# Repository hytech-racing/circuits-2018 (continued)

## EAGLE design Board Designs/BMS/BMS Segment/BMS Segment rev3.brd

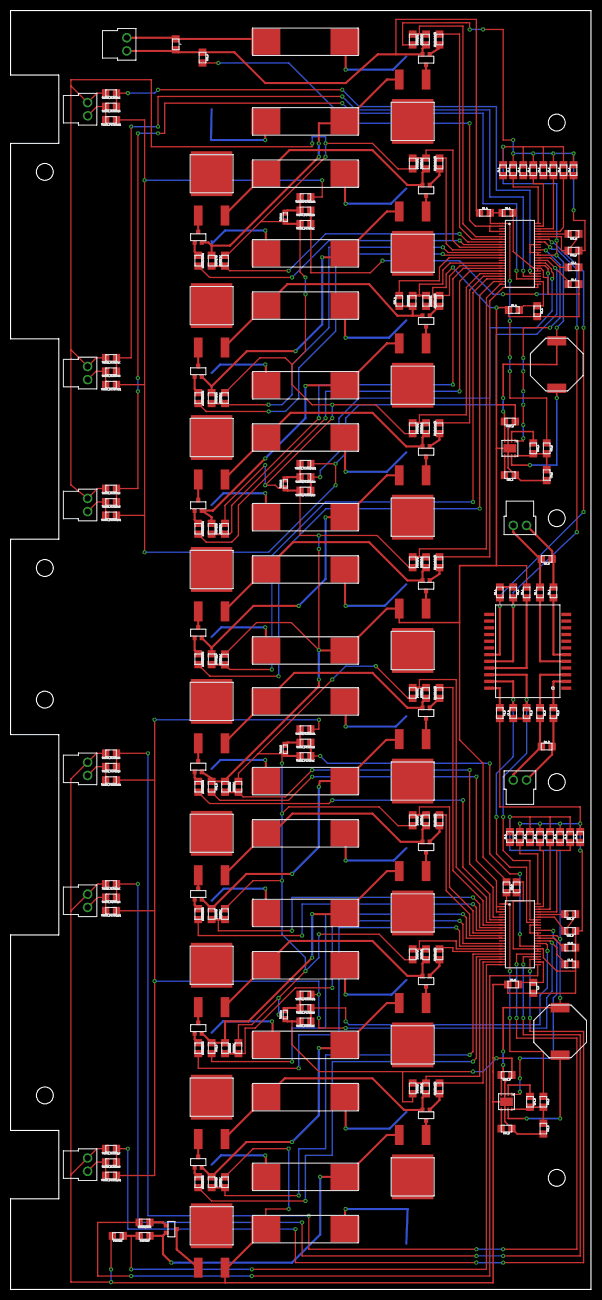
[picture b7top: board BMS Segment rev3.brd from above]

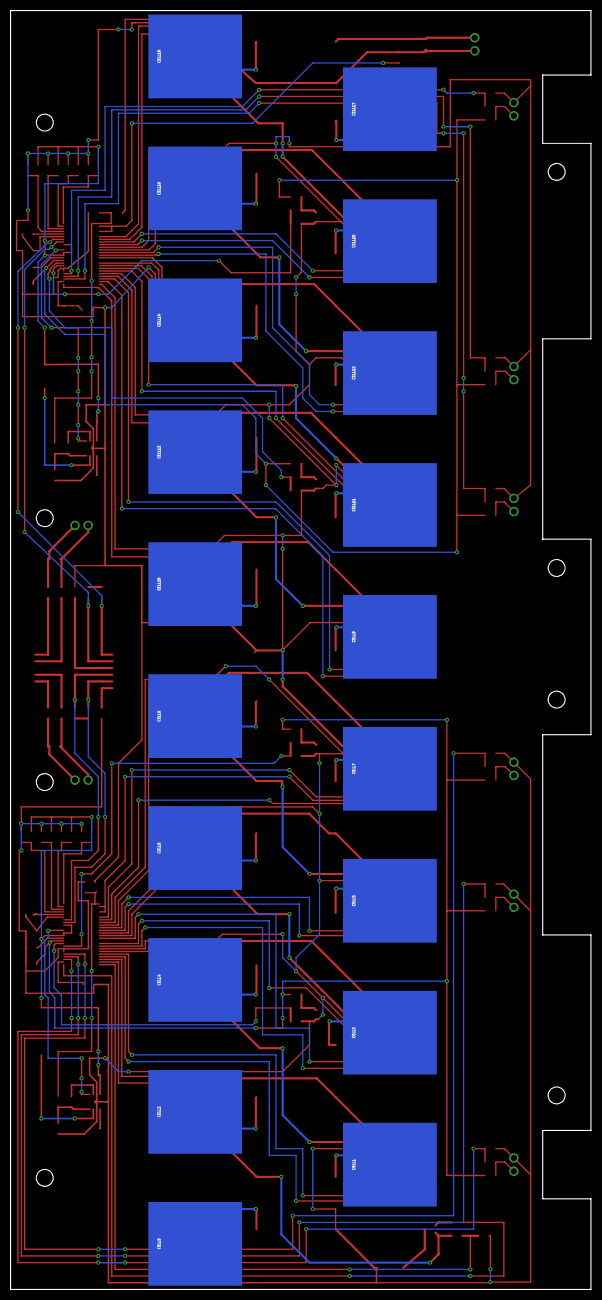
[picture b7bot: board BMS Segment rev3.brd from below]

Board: 2 copper layers, 110.0 x 242.3 mm, 237 parts (19 on the bottom side), 183 nets.

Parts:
AMS_TEST_PORT1: CONNECTOR-2NANO-FIT_VERTICAL-2; NANO-FIT_VERTICAL-2
BUCK_CONV_A: ADP2360; LFCSP-8
BUCK_CONV_B: ADP2360; LFCSP-8
C1_A, C1_B, C2_A, C2_B: 1uF; 0805
C3_A, C3_B: 15pF; 0805
C4_A, C4_B, C5_A: 10nF; 0805
C6_A, C6_B: 0.1uF; 0805
CELL0, CELL1, CELL2, CELL3, CELL4, CELL5, CELL6, CELL7, CELL8, CELL9, CELL10, CELL11, CELL12, CELL13, CELL14, CELL15, CELL16, CELL17, CELL18: BATTERY_SPRING_KEYSTONE5222; KEYSTONE5222
CIN_A: 4.7uF; 0805
CIN_B: 4.7uF; 0805
COUT_A: 22uF; 0805
COUT_B: 22uF; 0805
CSS_A: 2.2nF; 0805
CSS_B: 2.2nF; 0805
C_5: 10nF; 0805
DRAIN1:C, DRAIN2:C, DRAIN3:C, DRAIN4:C, DRAIN5:C, DRAIN6:C, DRAIN7:C, DRAIN8:C, DRAIN9:C, DRAIN10:C, DRAIN11:C, DRAIN12:C, DRAIN13:C, DRAIN14:C, DRAIN15:C, DRAIN16:C, DRAIN17:C, DRAIN18:C: 10nF; 0805
DRAIN1:DISCHARGE, DRAIN2:DISCHARGE, DRAIN3:DISCHARGE, DRAIN4:DISCHARGE, DRAIN5:DISCHARGE, DRAIN6:DISCHARGE, DRAIN7:DISCHARGE, DRAIN8:DISCHARGE, DRAIN9:DISCHARGE, DRAIN10:DISCHARGE, DRAIN11:DISCHARGE, DRAIN12:DISCHARGE, DRAIN13:DISCHARGE, DRAIN14:DISCHARGE, DRAIN15:DISCHARGE, DRAIN16:DISCHARGE, DRAIN17:DISCHARGE, DRAIN18:DISCHARGE: 5Ω; PWR163
DRAIN1:GATE, DRAIN2:GATE, DRAIN3:GATE, DRAIN4:GATE, DRAIN5:GATE, DRAIN6:GATE, DRAIN7:GATE, DRAIN8:GATE, DRAIN9:GATE, DRAIN10:GATE, DRAIN11:GATE, DRAIN12:GATE, DRAIN13:GATE, DRAIN14:GATE, DRAIN15:GATE, DRAIN16:GATE, DRAIN17:GATE, DRAIN18:GATE: 3.3kΩ; 0805
DRAIN1:PFET, DRAIN2:PFET, DRAIN3:PFET, DRAIN4:PFET, DRAIN5:PFET, DRAIN6:PFET, DRAIN7:PFET, DRAIN8:PFET, DRAIN9:PFET, DRAIN10:PFET, DRAIN11:PFET, DRAIN12:PFET, DRAIN13:PFET, DRAIN14:PFET, DRAIN15:PFET, DRAIN16:PFET, DRAIN17:PFET, DRAIN18:PFET: P-CHANNEL_MOSFET_DMP3099L-7; SOT23
DRAIN1:R, DRAIN2:R, DRAIN3:R, DRAIN4:R, DRAIN5:R, DRAIN6:R, DRAIN7:R, DRAIN8:R, DRAIN9:R, DRAIN10:R, DRAIN11:R, DRAIN12:R, DRAIN13:R, DRAIN14:R, DRAIN15:R, DRAIN16:R, DRAIN17:R, DRAIN18:R: 100Ω; 0805
F0, F1, F2, F3, F4, F5, F6, F7, F8, F9, F10, F11, F12, F13, F14, F15, F16, F17, F18: 0001.2704.11; 5X20MM_FUSE
ISOSPI_A: CONNECTOR-2NANO-FIT_VERTICAL-2; NANO-FIT_VERTICAL-2
ISOSPI_B: CONNECTOR-2NANO-FIT_VERTICAL-2; NANO-FIT_VERTICAL-2
J, J1_A, J1_B, J2_A, J2_B, J3_A, J3_B, J4_A, J4_B, J5_A, J5_B, J6_A, J6_B, J7_A, J7_B, J8_A, J8_B: 0805
L1_A, L1_B: 330uH; SRU1048
R1_A, R1_B, R2_A, R2_B: 100Ω; 0805
R3_A, R3_B: 402Ω; 0805
R4_A, R4_B, R5_A, R5_B: 22Ω; 0805
RB1_A, RB1_B: 1.2kΩ; 0805
RB2_A, RB2_B: 800Ω; 0805
RIN_A: 1kΩ; 0805
RIN_B: 1kΩ; 0805
RM_A: 100Ω; 0805
RM_B: 100Ω; 0805
RPG_A: 10MΩ; 0805
RPG_B: 10MΩ; 0805
RU1_A, RU1_B, RU2_A, RU2_B: 100Ω; 0805
THERM1, THERM2, THERM3, THERM4: 10kΩ; 0603
THERM1A, THERM1_B: Th1; NANO-FIT_VERTICAL-2
THERM2A, THERM2_B: Th2; NANO-FIT_VERTICAL-2
THERM3A, THERM3_B: Th3; NANO-FIT_VERTICAL-2
THERM_FILTER1:C, THERM_FILTER2:C, THERM_FILTER3:C, THERM_FILTER4:C, THERM_FILTER5:C, THERM_FILTER6:C, THERM_FILTER7:C, THERM_FILTER8:C, THERM_FILTER9:C, THERM_FILTER10:C: 10nF; 0805
THERM_FILTER1:R, THERM_FILTER2:R, THERM_FILTER3:R, THERM_FILTER4:R, THERM_FILTER5:R, THERM_FILTER6:R, THERM_FILTER7:R, THERM_FILTER8:R, THERM_FILTER9:R, THERM_FILTER10:R: 100Ω; 0805
THERM_FILTER1:R1, THERM_FILTER2:R1, THERM_FILTER3:R1, THERM_FILTER4:R1, THERM_FILTER5:R1, THERM_FILTER6:R1, THERM_FILTER7:R1, THERM_FILTER8:R1, THERM_FILTER9:R1, THERM_FILTER10:R1: 10kΩ; 0805
TRANSFORMER: SM51589PEL
U$1, U$2: LTC6804-2; LTC6804

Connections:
C0_A: C5_A.1, R2_A.2, U$1.26
C0_B: C_5.1, R2_B.2, U$2.26
C1_A: DRAIN10:C.1, DRAIN10:R.2, U$1.24
C1_B: DRAIN1:C.1, DRAIN1:R.2, U$2.24
C2_A: DRAIN11:C.1, DRAIN11:R.2, U$1.22
C2_B: DRAIN2:C.1, DRAIN2:R.2, U$2.22
C3_A: DRAIN12:C.1, DRAIN12:R.2, U$1.20
C3_B: DRAIN3:C.1, DRAIN3:R.2, U$2.20
C4_A: DRAIN13:C.1, DRAIN13:R.2, U$1.18
C4_B: DRAIN4:C.1, DRAIN4:R.2, U$2.18
C5_A: DRAIN14:C.1, DRAIN14:R.2, U$1.16
C5_B: DRAIN5:C.1, DRAIN5:R.2, U$2.16
C7_A: DRAIN15:C.1, DRAIN15:R.2, U$1.12
C7_B: DRAIN6:C.1, DRAIN6:R.2, U$2.12
C8_A: DRAIN16:C.1, DRAIN16:R.2, U$1.10
C8_B: DRAIN7:C.1, DRAIN7:R.2, U$2.10
C9_A: DRAIN17:C.1, DRAIN17:R.2, U$1.8
C9_B: DRAIN8:C.1, DRAIN8:R.2, U$2.8
C10_A: DRAIN18:C.1, DRAIN18:R.2, U$1.6
C10_B: DRAIN9:C.1, DRAIN9:R.2, U$2.6
CC0: CELL0.P$1, F0.P$1
CC1: CELL1.P$1, F1.P$1
CC2: CELL2.P$1, F2.P$1
CC3: CELL3.P$1, F3.P$1
CC4: CELL4.P$1, F4.P$1
CC5: CELL5.P$1, F5.P$1
CC6: CELL6.P$1, F6.P$1
CC7: CELL7.P$1, F7.P$1
CC8: CELL8.P$1, F8.P$1
CC9: CELL9.P$1, F9.P$1
CC10: CELL10.P$1, F10.P$1
CC11: CELL11.P$1, F11.P$1
CC12: CELL12.P$1, F12.P$1
CC13: CELL13.P$1, F13.P$1
CC14: CELL14.P$1, F14.P$1
CC15: CELL15.P$1, F15.P$1
CC16: CELL16.P$1, F16.P$1
CC17: CELL17.P$1, F17.P$1
CC18: CELL18.P$1, F18.P$1
DRAIN1:GATE: DRAIN1:GATE.1, DRAIN1:PFET.1
DRAIN1:N$1: DRAIN1:DISCHARGE.1, DRAIN1:PFET.3
DRAIN2:GATE: DRAIN2:GATE.1, DRAIN2:PFET.1
DRAIN2:N$1: DRAIN2:DISCHARGE.1, DRAIN2:PFET.3
DRAIN3:GATE: DRAIN3:GATE.1, DRAIN3:PFET.1
DRAIN3:N$1: DRAIN3:DISCHARGE.1, DRAIN3:PFET.3
DRAIN4:GATE: DRAIN4:GATE.1, DRAIN4:PFET.1
DRAIN4:N$1: DRAIN4:DISCHARGE.1, DRAIN4:PFET.3
DRAIN5:GATE: DRAIN5:GATE.1, DRAIN5:PFET.1
DRAIN5:N$1: DRAIN5:DISCHARGE.1, DRAIN5:PFET.3
DRAIN6:GATE: DRAIN6:GATE.1, DRAIN6:PFET.1
DRAIN6:N$1: DRAIN6:DISCHARGE.1, DRAIN6:PFET.3
DRAIN7:GATE: DRAIN7:GATE.1, DRAIN7:PFET.1
DRAIN7:N$1: DRAIN7:DISCHARGE.1, DRAIN7:PFET.3
DRAIN8:GATE: DRAIN8:GATE.1, DRAIN8:PFET.1
DRAIN8:N$1: DRAIN8:DISCHARGE.1, DRAIN8:PFET.3
DRAIN9:GATE: DRAIN9:GATE.1, DRAIN9:PFET.1
DRAIN9:N$1: DRAIN9:DISCHARGE.1, DRAIN9:PFET.3
DRAIN10:GATE: DRAIN10:GATE.1, DRAIN10:PFET.1
DRAIN10:N$1: DRAIN10:DISCHARGE.1, DRAIN10:PFET.3
DRAIN11:GATE: DRAIN11:GATE.1, DRAIN11:PFET.1
DRAIN11:N$1: DRAIN11:DISCHARGE.1, DRAIN11:PFET.3
DRAIN12:GATE: DRAIN12:GATE.1, DRAIN12:PFET.1
DRAIN12:N$1: DRAIN12:DISCHARGE.1, DRAIN12:PFET.3
DRAIN13:GATE: DRAIN13:GATE.1, DRAIN13:PFET.1
DRAIN13:N$1: DRAIN13:DISCHARGE.1, DRAIN13:PFET.3
DRAIN14:GATE: DRAIN14:GATE.1, DRAIN14:PFET.1
DRAIN14:N$1: DRAIN14:DISCHARGE.1, DRAIN14:PFET.3
DRAIN15:GATE: DRAIN15:GATE.1, DRAIN15:PFET.1
DRAIN15:N$1: DRAIN15:DISCHARGE.1, DRAIN15:PFET.3
DRAIN16:GATE: DRAIN16:GATE.1, DRAIN16:PFET.1
DRAIN16:N$1: DRAIN16:DISCHARGE.1, DRAIN16:PFET.3
DRAIN17:GATE: DRAIN17:GATE.1, DRAIN17:PFET.1
DRAIN17:N$1: DRAIN17:DISCHARGE.1, DRAIN17:PFET.3
DRAIN18:GATE: DRAIN18:GATE.1, DRAIN18:PFET.1
DRAIN18:N$1: DRAIN18:DISCHARGE.1, DRAIN18:PFET.3
DRIVE_A: BUCK_CONV_A.1, U$1.38
DRIVE_B: BUCK_CONV_B.1, U$2.38
GPIO1_A: THERM_FILTER6:C.1, THERM_FILTER6:R.1, U$1.27
GPIO1_B: THERM_FILTER1:C.1, THERM_FILTER1:R.1, U$2.27
GPIO2_A: THERM_FILTER7:C.1, THERM_FILTER7:R.1, U$1.28
GPIO2_B: THERM_FILTER2:C.1, THERM_FILTER2:R.1, U$2.28
GPIO3_A: THERM_FILTER8:C.1, THERM_FILTER8:R.1, U$1.29
GPIO3_B: THERM_FILTER3:C.1, THERM_FILTER3:R.1, U$2.29
GPIO4_A: THERM_FILTER9:C.1, THERM_FILTER9:R.1, U$1.32
GPIO4_B: THERM_FILTER4:C.1, THERM_FILTER4:R.1, U$2.32
GPIO5_A: THERM_FILTER10:C.1, THERM_FILTER10:R.1, U$1.33
GPIO5_B: THERM_FILTER5:C.1, THERM_FILTER5:R.1, U$2.33
IM_A: C3_A.2, TRANSFORMER.20, U$1.41
IM_B: C3_B.2, TRANSFORMER.23, U$2.41
IP_A: R3_A.1, TRANSFORMER.19, U$1.42
IP_B: R3_B.1, TRANSFORMER.22, U$2.42
ISOSPI-M_A: ISOSPI_A.P$2, R5_A.2, RM_A.2
ISOSPI-M_B: ISOSPI_B.P$2, R5_B.2, RM_B.2
ISOSPI-P_A: ISOSPI_A.P$1, R4_A.2, RM_A.1
ISOSPI-P_B: ISOSPI_B.P$1, R4_B.2, RM_B.1
unnamed: C4_B.1, TRANSFORMER.24
unnamed: RB1_B.2, U$2.44
unnamed: THERM1_B.P$2, THERM_FILTER1:R.2, THERM_FILTER1:R1.2
unnamed: RB1_B.1, RB2_B.2, U$2.43
unnamed: R4_B.1, TRANSFORMER.3
unnamed: RB1_A.2, U$1.44
unnamed: R5_B.1, TRANSFORMER.2
unnamed: J7_B.1, J8_B.1, U$2.48
unnamed: J5_B.1, J6_B.1, U$2.47
unnamed: C3_B.1, R3_B.2
unnamed: BUCK_CONV_B.8, CIN_B.1, RIN_B.2, RPG_B.2
unnamed: BUCK_CONV_B.2, RPG_B.1
unnamed: J3_B.1, J4_B.1, U$2.46
unnamed: BUCK_CONV_B.5, CSS_B.2
unnamed: BUCK_CONV_B.7, L1_B.1
unnamed: J1_B.1, J2_B.1, U$2.45
unnamed: THERM4.2, THERM_FILTER5:R.2, THERM_FILTER5:R1.2
unnamed: THERM2_B.P$2, THERM_FILTER2:R.2, THERM_FILTER2:R1.2
unnamed: THERM3.2, THERM_FILTER4:R.2, THERM_FILTER4:R1.2
unnamed: RB1_A.1, RB2_A.2, U$1.43
unnamed: C4_A.1, TRANSFORMER.21
unnamed: R4_A.1, TRANSFORMER.6
unnamed: R5_A.1, TRANSFORMER.5
unnamed: C3_A.1, R3_A.2
unnamed: BUCK_CONV_A.8, CIN_A.1, RIN_A.2, RPG_A.2
unnamed: THERM3_B.P$2, THERM_FILTER3:R.2, THERM_FILTER3:R1.2
unnamed: BUCK_CONV_A.2, RPG_A.1
unnamed: BUCK_CONV_A.5, CSS_A.2
unnamed: BUCK_CONV_A.7, L1_A.1
unnamed: J7_A.1, J8_A.1, U$1.48
unnamed: J5_A.1, J6_A.1, U$1.47
unnamed: J3_A.1, J4_A.1, U$1.46
unnamed: J1_A.1, J2_A.1, U$1.45
unnamed: THERM1.2, THERM_FILTER9:R.2, THERM_FILTER9:R1.2
unnamed: THERM3A.P$2, THERM_FILTER8:R.2, THERM_FILTER8:R1.2
unnamed: THERM2.2, THERM_FILTER10:R.2, THERM_FILTER10:R1.2
unnamed: THERM2A.P$2, THERM_FILTER7:R.2, THERM_FILTER7:R1.2
unnamed: THERM1A.P$2, THERM_FILTER6:R.2, THERM_FILTER6:R1.2
S1_A: DRAIN10:GATE.2, U$1.25
S1_B: DRAIN1:GATE.2, U$2.25
S2_A: DRAIN11:GATE.2, U$1.23
S2_B: DRAIN2:GATE.2, U$2.23
S3_A: DRAIN12:GATE.2, U$1.21
S3_B: DRAIN3:GATE.2, U$2.21
S4_A: DRAIN13:GATE.2, U$1.19
S4_B: DRAIN4:GATE.2, U$2.19
S5_A: DRAIN14:GATE.2, U$1.17
S5_B: DRAIN5:GATE.2, U$2.17
S7_A: DRAIN15:GATE.2, U$1.13
S7_B: DRAIN6:GATE.2, U$2.13
S8_A: DRAIN16:GATE.2, U$1.11
S8_B: DRAIN7:GATE.2, U$2.11
S9_A: DRAIN17:GATE.2, U$1.9
S9_B: DRAIN8:GATE.2, U$2.9
S10_A: DRAIN18:GATE.2, U$1.7
S10_B: DRAIN9:GATE.2, U$2.7
SENSE1: DRAIN1:PFET.2, DRAIN1:R.1, DRAIN2:DISCHARGE.2, F1.P$2
SENSE2: DRAIN2:PFET.2, DRAIN2:R.1, DRAIN3:DISCHARGE.2, F2.P$2
SENSE3: DRAIN3:PFET.2, DRAIN3:R.1, DRAIN4:DISCHARGE.2, F3.P$2
SENSE4: DRAIN4:PFET.2, DRAIN4:R.1, DRAIN5:DISCHARGE.2, F4.P$2
SENSE5: DRAIN5:PFET.2, DRAIN5:R.1, DRAIN6:DISCHARGE.2, F5.P$2, RU2_B.1
SENSE6: DRAIN6:PFET.2, DRAIN6:R.1, DRAIN7:DISCHARGE.2, F6.P$2
SENSE7: DRAIN7:PFET.2, DRAIN7:R.1, DRAIN8:DISCHARGE.2, F7.P$2
SENSE8: DRAIN8:PFET.2, DRAIN8:R.1, DRAIN9:DISCHARGE.2, F8.P$2
SENSE10: DRAIN10:PFET.2, DRAIN10:R.1, DRAIN11:DISCHARGE.2, F10.P$2
SENSE11: DRAIN11:PFET.2, DRAIN11:R.1, DRAIN12:DISCHARGE.2, F11.P$2
SENSE12: DRAIN12:PFET.2, DRAIN12:R.1, DRAIN13:DISCHARGE.2, F12.P$2
SENSE13: DRAIN13:PFET.2, DRAIN13:R.1, DRAIN14:DISCHARGE.2, F13.P$2
SENSE14: DRAIN14:PFET.2, DRAIN14:R.1, DRAIN15:DISCHARGE.2, F14.P$2, RU2_A.1
SENSE15: DRAIN15:PFET.2, DRAIN15:R.1, DRAIN16:DISCHARGE.2, F15.P$2
SENSE16: DRAIN16:PFET.2, DRAIN16:R.1, DRAIN17:DISCHARGE.2, F16.P$2
SENSE17: DRAIN17:PFET.2, DRAIN17:R.1, DRAIN18:DISCHARGE.2, F17.P$2
SENSE18: AMS_TEST_PORT1.P$2, DRAIN18:PFET.2, DRAIN18:R.1, J.2, R1_A.1, RU1_A.1
SENSE18_J: AMS_TEST_PORT1.P$1, F18.P$2, J.1
UNUSED1_A: RU1_A.2, U$1.2, U$1.4
UNUSED1_B: RU1_B.2, U$2.2, U$2.4
UNUSED2_A: RU2_A.2, U$1.14
UNUSED2_B: RU2_B.2, U$2.14
V+_A: C6_A.1, R1_A.2, RIN_A.1, U$1.1
V+_B: C6_B.1, R1_B.2, RIN_B.1, U$2.1
V-_A: BUCK_CONV_A.3, BUCK_CONV_A.6, BUCK_CONV_A.PAD, C1_A.2, C2_A.2, C4_A.2, C5_A.2, C6_A.2, CIN_A.2, COUT_A.1, CSS_A.1, DRAIN9:PFET.2, DRAIN9:R.1, DRAIN10:C.2, DRAIN10:DISCHARGE.2, DRAIN11:C.2, DRAIN12:C.2, DRAIN13:C.2, DRAIN14:C.2, DRAIN15:C.2, DRAIN16:C.2, DRAIN17:C.2, DRAIN18:C.2, F9.P$2, J1_A.2, J3_A.2, J5_A.2, J7_A.2, R1_B.1, R2_A.1, RB2_A.1, RU1_B.1, THERM1.1, THERM1A.P$1, THERM2.1, THERM2A.P$1, THERM3A.P$1, THERM_FILTER6:C.2, THERM_FILTER7:C.2, THERM_FILTER8:C.2, THERM_FILTER9:C.2, THERM_FILTER10:C.2, U$1.30, U$1.31
V-_B: BUCK_CONV_B.3, BUCK_CONV_B.6, BUCK_CONV_B.PAD, C1_B.2, C2_B.2, C4_B.2, C6_B.2, CIN_B.2, COUT_B.1, CSS_B.1, C_5.2, DRAIN1:C.2, DRAIN1:DISCHARGE.2, DRAIN2:C.2, DRAIN3:C.2, DRAIN4:C.2, DRAIN5:C.2, DRAIN6:C.2, DRAIN7:C.2, DRAIN8:C.2, DRAIN9:C.2, F0.P$2, J1_B.2, J3_B.2, J5_B.2, J7_B.2, R2_B.1, RB2_B.1, THERM1_B.P$1, THERM2_B.P$1, THERM3.1, THERM3_B.P$1, THERM4.1, THERM_FILTER1:C.2, THERM_FILTER2:C.2, THERM_FILTER3:C.2, THERM_FILTER4:C.2, THERM_FILTER5:C.2, U$2.30, U$2.31
VREF1_A: C2_A.1, U$1.35
VREF1_B: C2_B.1, U$2.35
VREF2_A: C1_A.1, THERM_FILTER6:R1.1, THERM_FILTER7:R1.1, THERM_FILTER8:R1.1, THERM_FILTER9:R1.1, THERM_FILTER10:R1.1, U$1.34
VREF2_B: C1_B.1, THERM_FILTER1:R1.1, THERM_FILTER2:R1.1, THERM_FILTER3:R1.1, THERM_FILTER4:R1.1, THERM_FILTER5:R1.1, U$2.34
VREG_A: BUCK_CONV_A.4, COUT_A.2, J2_A.2, J4_A.2, J6_A.2, J8_A.2, L1_A.2, U$1.36, U$1.37, U$1.40
VREG_B: BUCK_CONV_B.4, COUT_B.2, J2_B.2, J4_B.2, J6_B.2, J8_B.2, L1_B.2, U$2.36, U$2.37, U$2.40
